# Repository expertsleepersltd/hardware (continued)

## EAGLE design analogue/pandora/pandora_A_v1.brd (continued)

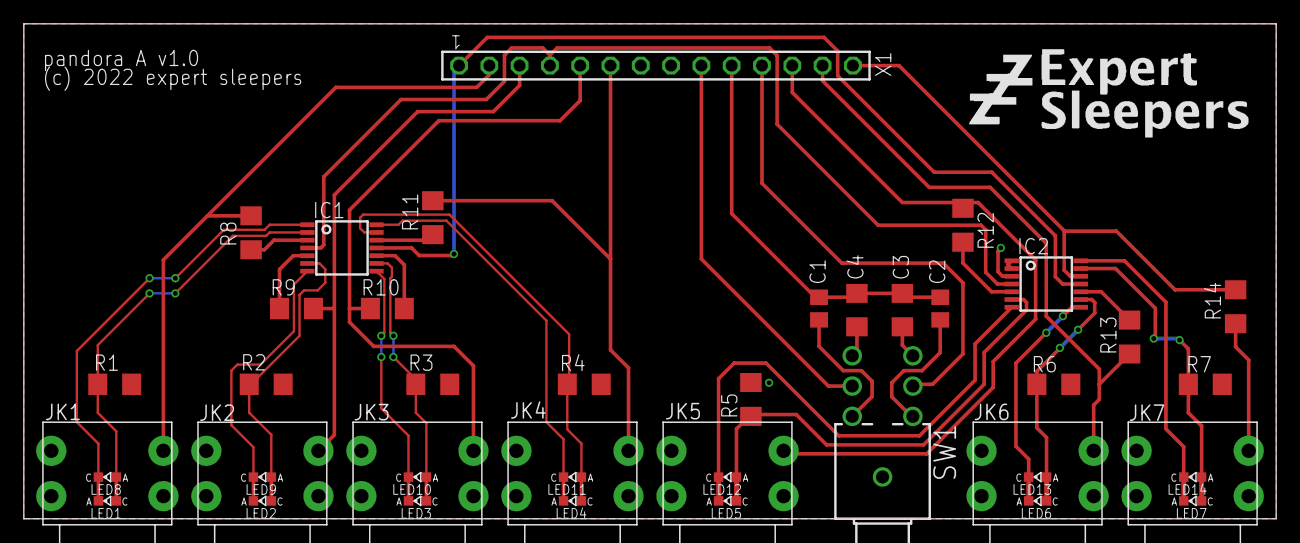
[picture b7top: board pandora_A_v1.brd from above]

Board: 2 copper layers, 105.0 x 41.5 mm, 44 parts (0 on the bottom side), 39 nets.

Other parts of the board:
U$1: ES_ZZZ_TEXT_TPLACE_1IN_600DPI
